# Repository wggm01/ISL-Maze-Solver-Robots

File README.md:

# Maze-Solver-Robots
We are working on a proposal to teach secondary teachers how to develop robots that are capable of solving a maze using open source platforms like Arduino and Raspberry.

Project Members:

Javier Romero.
> 

Fatima Batista.
> 

Sobenis.
> 

Gabriel Marzullo.
> 

Logistical info: 

Team Name: Intelligent-Systems-Laboratory

Organization: Technological University of Panama

Country: Panama 

Contact person: Danilo Caceres 

Email: danilo.caceres@utp.ac.pa

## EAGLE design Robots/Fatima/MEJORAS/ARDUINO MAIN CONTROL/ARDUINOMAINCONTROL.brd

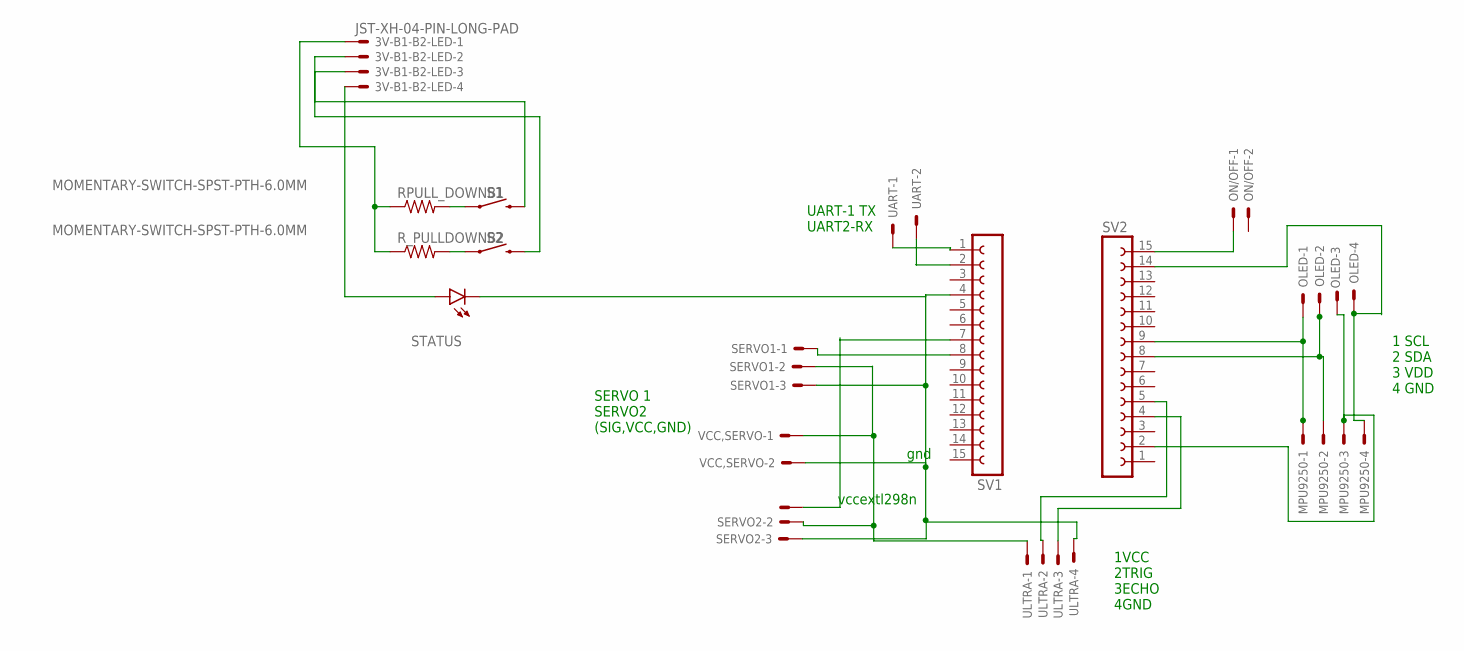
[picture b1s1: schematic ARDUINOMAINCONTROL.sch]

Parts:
3V-B1-B2-LED: JST-XH-04-PIN-LONG-PAD; JST-XH-04-PACKAGE-LONG-PAD
MPU9250: JST-XH-04-PIN-LONG-PAD; JST-XH-04-PACKAGE-LONG-PAD
OLED: JST-XH-04-PIN-LONG-PAD; JST-XH-04-PACKAGE-LONG-PAD
ON/OFF: JST-XH-02-PIN-LONG-PAD; JST-XH-02-PACKAGE-LONG-PAD
RPULL_DOWNB1: R-US_0207/10; 0207/10
R_PULLDOWNB2: R-US_0207/10; 0207/10
S1, S2: MOMENTARY-SWITCH-SPST-PTH-6.0MM; TACTILE_SWITCH_PTH_6.0MM
SERVO1, SERVO2: JST-XH-03-PIN-LONG-PAD; JST-XH-03-PACKAGE-LONG-PAD
STATUS: LED3MM
SV1, SV2: FE15-1; FE15
UART: JST-XH-02-PIN-LONG-PAD; JST-XH-02-PACKAGE-LONG-PAD
ULTRA: JST-XH-04-PIN-LONG-PAD; JST-XH-04-PACKAGE-LONG-PAD
VCC,SERVO: JST-XH-02-PIN-LONG-PAD; JST-XH-02-PACKAGE-LONG-PAD

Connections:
unnamed: MPU9250.1, OLED.1, SV2.9
unnamed: MPU9250.3, OLED.3, SV2.2
unnamed: MPU9250.4, OLED.4, SV2.14
unnamed: ON/OFF.1, SV2.15
unnamed: SV1.1, UART.1
unnamed: SV1.2, UART.2
unnamed: SERVO1.3, STATUS.K (C), SV1.4, ULTRA.4, VCC,SERVO.2
unnamed: SERVO1.2, ULTRA.1, VCC,SERVO.1
unnamed: SV2.4, ULTRA.3
unnamed: SV2.5, ULTRA.2
unnamed: RPULL_DOWNB1.2, S1.1
unnamed: R_PULLDOWNB2.2, S2.1
unnamed: SERVO1.1, SV1.8
unnamed: SERVO2.1, SV1.7
unnamed: 3V-B1-B2-LED.1, RPULL_DOWNB1.1, R_PULLDOWNB2.1
unnamed: 3V-B1-B2-LED.2, S1.3 (2)
unnamed: 3V-B1-B2-LED.3, S2.3 (2)
unnamed: 3V-B1-B2-LED.4, STATUS.A
unnamed: MPU9250.2, OLED.2, SV2.8

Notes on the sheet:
1 SCL 2 SDA 3 VDD 4 GND
UART-1 TX UART2-RX
SERVO 1 SERVO2 (SIG,VCC,GND)
1VCC 2TRIG 3ECHO 4GND
gnd
vccextl298n

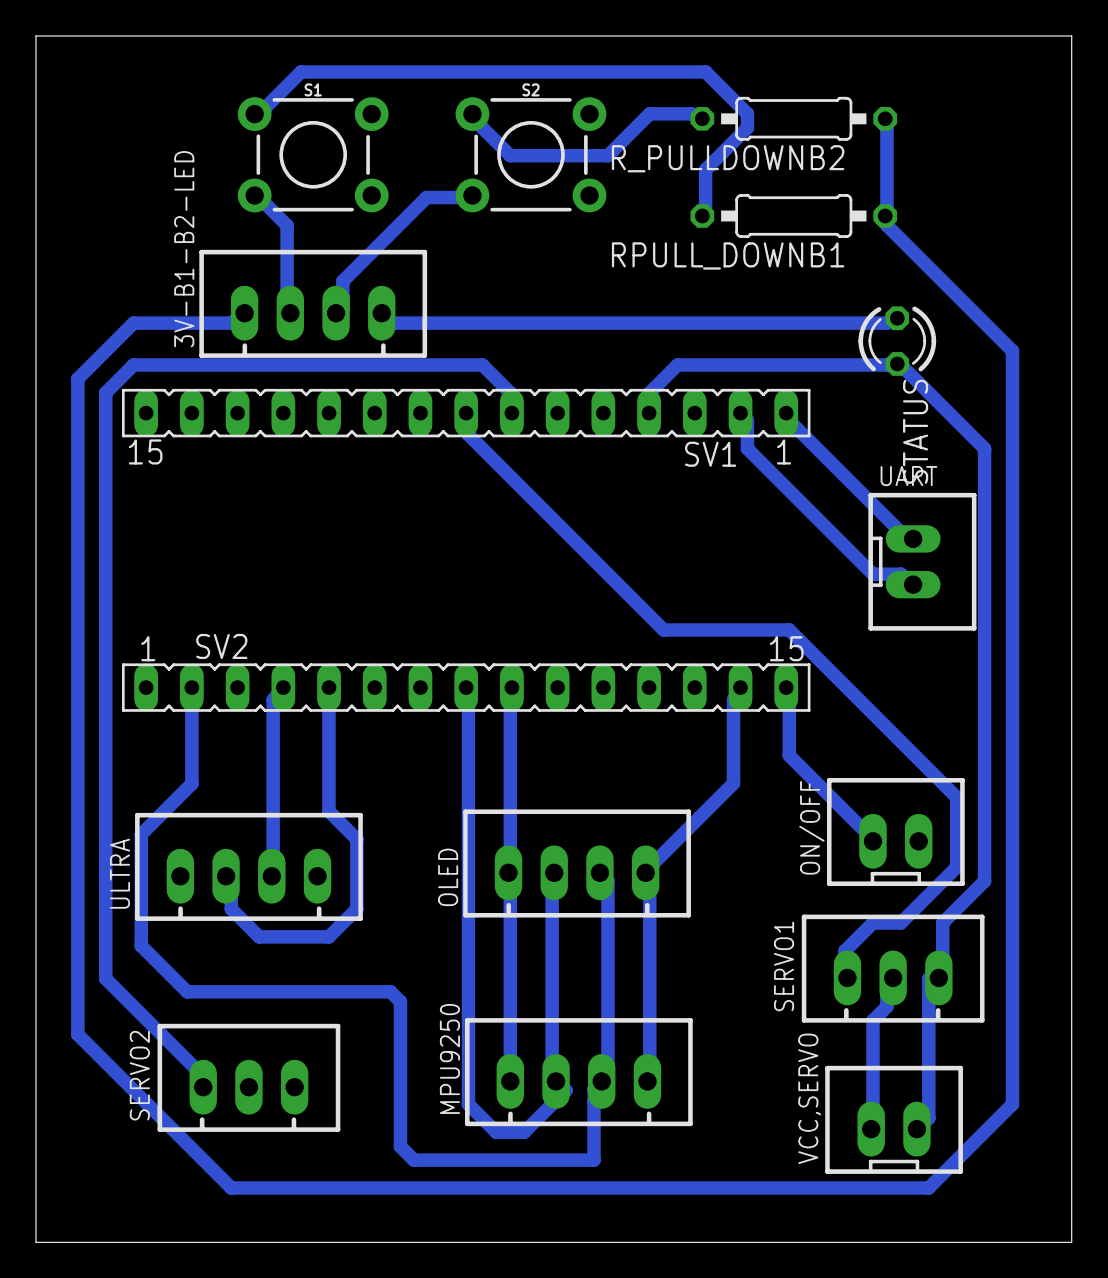
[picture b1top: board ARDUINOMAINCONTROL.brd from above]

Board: 2 copper layers, 57.5 x 67.0 mm, 16 parts (0 on the bottom side), 19 nets.

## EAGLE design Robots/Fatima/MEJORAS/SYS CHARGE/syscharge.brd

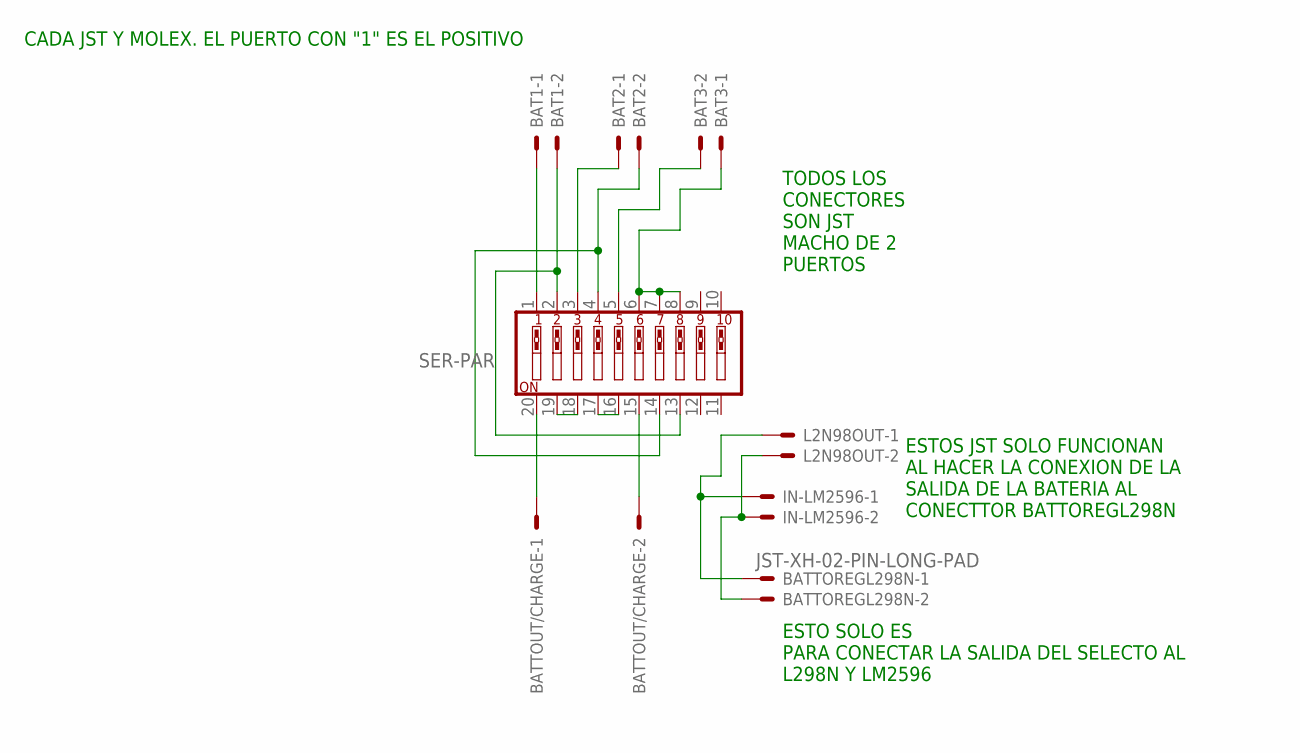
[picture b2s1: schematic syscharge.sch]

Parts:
BAT1, BAT2, BAT3: JST-XH-02-PIN-LONG-PAD; JST-XH-02-PACKAGE-LONG-PAD
BATTOREGL298N: JST-XH-02-PIN-LONG-PAD; JST-XH-02-PACKAGE-LONG-PAD
BATTOUT/CHARGE: JST-XH-02-PIN-LONG-PAD; JST-XH-02-PACKAGE-LONG-PAD
IN-LM2596: JST-XH-02-PIN-LONG-PAD; JST-XH-02-PACKAGE-LONG-PAD
L2N98OUT: JST-XH-02-PIN-LONG-PAD; JST-XH-02-PACKAGE-LONG-PAD
SER-PAR: SW_DIP-10; EDG-10

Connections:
unnamed: BAT1.2, SER-PAR.2, SER-PAR.13
unnamed: BAT2.1, SER-PAR.3
unnamed: BAT2.2, SER-PAR.4, SER-PAR.14
unnamed: BAT3.2, SER-PAR.5
unnamed: BATTOUT/CHARGE.2, SER-PAR.15
unnamed: SER-PAR.18, SER-PAR.19
unnamed: SER-PAR.16, SER-PAR.17
unnamed: BAT3.1, SER-PAR.6, SER-PAR.7, SER-PAR.8
unnamed: BATTOREGL298N.1, IN-LM2596.1, L2N98OUT.1
unnamed: BATTOREGL298N.2, IN-LM2596.2, L2N98OUT.2
unnamed: BAT1.1, SER-PAR.1
unnamed: BATTOUT/CHARGE.1, SER-PAR.20

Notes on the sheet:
CADA JST Y MOLEX. EL PUERTO CON "1" ES EL POSITIVO
ESTOS JST SOLO FUNCIONAN AL HACER LA CONEXION DE LA SALIDA DE LA BATERIA AL CONECTTOR BATTOREGL298N
TODOS LOS CONECTORES SON JST MACHO DE 2 PUERTOS
ESTO SOLO ES PARA CONECTAR LA SALIDA DEL SELECTO AL L298N Y LM2596

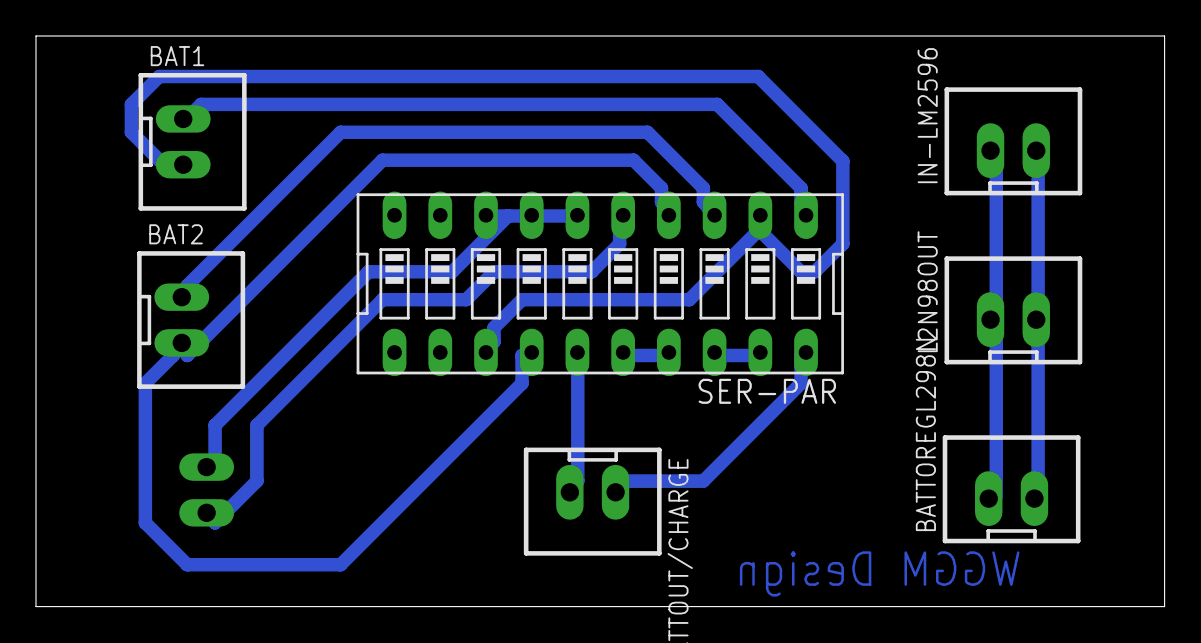
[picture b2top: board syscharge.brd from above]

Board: 2 copper layers, 62.7 x 31.7 mm, 8 parts (1 on the bottom side), 12 nets.

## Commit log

2019-02-28 Updating
2019-03-03 Elminando vieja toma de datos
2019-03-12 upadting
2019-03-13 MultiClients Code
2019-03-13 Prueba sin Analizar data de mpu9250
2019-03-13 updating codes
2019-03-14 Solo falta data imu corregida
2019-03-15 solo falta ajustar tiempo de integracion
2019-03-16 diseñando
2019-03-16 Listo para manufacturar y armar
2019-03-16 competitors
2019-03-17 Codigo unido
2019-03-17 Codigo unido y listo para pruebas
2019-03-18 control de ejecucion por probar
2019-03-19 archivos no utiles
2019-03-20 Circuit Project and Gcode to mill
2019-03-20 error moviendo archivos
2019-03-20 arreglando cnc
2019-03-20 Sobenis Modificacion
    regreso de sonicos, cogida de motores y l298n
2019-03-21 cambios a pcb
2019-03-21 nuevo diseño para probar
    el codigo g esta para tip diameter 0.2mm trazas a 0.11mm(30 grados), grosor de placa 1.55, drills a 0.8mm
2019-03-22 DID T
2019-03-24 correciones antes de pruebas
2019-03-26 reduccion de codigos
2019-03-26 ready for first test
2019-03-28 Piezas Sobenis
    Regreso de Piezas Sibenis
2019-03-29 update processing
2019-03-31 nuevo intento rpi alone
2019-03-31 LISTO PARA PROBAR
    INSTALAR LIBRERIA DE MPU 9250 Y HACER ECUACION PARA SERVO. AH PROBAR SE HA DICHO
2019-04-02 mejoras
2019-04-12 prueba, arduino carga con logica
2019-04-21 intento de regresion linear
2019-04-23 Simulaciones de codigo
    Mejoras requeridas en la adquisicion de data, problemas con valores 80 que significan no objeto. posible solucion disminuir baudrate.
2019-04-24 arreglo luego del merge
2019-04-24 prueba con dos barridos
    resultados iguales, decepcion emocional
2019-04-24 fixed
2019-04-25 reducciond e velocidad de baudios
2019-04-25 mas pruebas
2019-04-26 Listo para recoleccion de data en movimiento
2019-04-28 Cambio en logica de radar
    Se espera mejora en la toma de lecturas
2019-04-29 Holi
2019-04-30 Diagrama de bloques de nueva pcb
2019-04-30 mejora radar
2019-04-30 arreglando desastre
2019-05-01 ultimos cambios
2019-05-01 wrong folder
2019-05-02 nuevo codigo de simulacion
2019-05-03 diosesquchomisplegarias
2019-05-04 Update rpiard.py
    Funcion txdata actualizada con adaptacion de paquetes a 8 bytes, control de fin de visualizacion agregada, falta hacer servidor bluetooth y probar
2019-05-06 Codigos optimizados
    EN EL PC QUE HARA LA VISUALIZACION DAR PRIORIDAD AL SCRIPT PARA EVITAR RETRASOS EN EL STREAMING
2019-05-10 servidor de bluetooth corre en paralelo
2019-05-17 cambios requeridos para optimizar codigo
    se requieren realizar pruebas manuales y cargar bateria.
2019-05-18 Resultados de pruebas
2019-05-18 Reduccion de caida de voltaje en L298N
    el led bajaba su intencidad debido a que el servo al llegar al extremo hacia mucho esfuerzo.
2019-05-19 maze, plotter
2019-05-29 Actualizacion de piezas ROBOCUP MAZE
2019-06-17 new parts
2019-06-19 ta ta tan
2019-06-20 actualizando
2019-08-06 Create implementacion de encoder
2019-08-07 Log desconocido
2019-08-07 codigos implementados
    CODIGO PARA ENCODER
    CODIGO PARA CONTROL DE MOTORES DESDE LA RASPBERRY
    ESPERANDO PARA REVISION.
2019-08-08 mismo cambio omitir
2019-08-20 ya valio

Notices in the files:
parts and their libraries:
SparkFun-Switches: Licensing: Creative Commons ShareAlike 4.0 International - https://creativecommons.org/licenses/by-sa/4.0
